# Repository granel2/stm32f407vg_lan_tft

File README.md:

# stm32f407vg_lan_tft

STM32F407VGT6 + LAN8720 (Ethernet, lwIP, DHCP, TCP-клиент) + 3.5" TFT-дисплей.
Проект основан на `stm32f407vg_lan_v1` (Ethernet-часть отлажена и работает, см. `docs/`).

## Структура

| Путь | Что это |
|---|---|
| `Core/Inc`, `Core/Src`, `Core/Startup` | Ethernet/lwIP-часть: HAL MSP, прерывания, lwIP-порт (`ethernetif.c`), TCP-клиент, `main.c` |
| `Display/` | Весь дисплейный модуль, обособлен от Ethernet-кода — см. `Display/README.md` |
| `Config/` | Постоянные настройки (сервер/имя/статический IP) + веб-страница настройки `http://<IP модуля>/` (порт 80) + TCP-конфигуратор на порту 7000 — см. `Config/README.md` |
| `Keypad/` | Приём пакетов от модуля клавиатуры 4×4 (ATmega328P) на SV5: I2C1-ведомый `0x30`, на регистрах — см. `Keypad/README.md` |
| `Drivers/` | STM32Cube HAL F4 V1.28.3, CMSIS, драйвер PHY lan8742 |
| `Middlewares/Third_Party/LwIP` | lwIP (NO_SYS=1) |
| `CMakeLists.txt`, `CMakePresets.json`, `toolchain-arm-none-eabi.cmake`, `linker_script.ld` | Сборка |
| `stm32f407vg_lan_tft.ioc`, `.mxproject` | Проект CubeMX — **только справочно**: ETH и часть периферии добавлены руками, перегенерировать код из CubeMX нельзя |
| `hardware/` | `BOARD.md` — выжимка по плате (разъёмы, питание, выводы); схема и плата (Eagle) `f407.sch`/`f407.brd`, распечатка схемы `f407_schematic_A3.pdf` |
| `docs/` | История отладки Ethernet (`PROJECT_GUIDE.md`), аппаратный фикс LAN8720 (`CHANGES_LAN8720.md`), заметки по сборке, даташиты |
| `stm32f407vg_lan_tft.code-workspace` | Workspace VS Code |

## Целевая платформа

- MCU STM32F407VGT6 (LQFP100), HSE 25 MHz, SYSCLK 160 MHz, APB1 40 MHz, APB2 80 MHz
- USART1 (PA9/PA10) и USART3 (PD8/PD9), 921600 baud — отладочный лог
- ETH RMII → LAN8720 (REFCLK на PA1), см. `docs/CHANGES_LAN8720.md` про обязательный резистор 1 кОм на страпе nINTSEL
- LED: PB4, PB5, PD0, PD1, PD4, PD7

## Сборка

Требуется `arm-none-eabi-gcc`, `cmake ≥ 3.24`, `ninja`, `openocd` в `PATH`.

```powershell
cmake --preset default          # конфигурация (build/, Ninja, toolchain-файл)
cmake --build --preset default  # сборка → build/stm32f407vg_lan_tft.{elf,bin,hex,map}
```

В VS Code: `Terminal → Run Task → CMake: Configure`, затем `CMake: Build` (Ctrl+Shift+B).

## Прошивка и отладка

- Задача VS Code `Flash STM32F407VG` — `scripts/flash-progress.ps1`, обёртка над той же
  последовательностью OpenOCD (`init` → `reset halt` → `mass_erase` → `write_image` →
  `verify_image` → `reset run`; ST-Link). Команда `program … verify` в текущей сборке
  OpenOCD глючит — подробности в `docs/PROJECT_GUIDE.md`, поэтому по-прежнему используется
  явная последовательность, а не `program`. Обёртка добавляет текстовую шкалу прогресса
  в терминал (OpenOCD сам не печатает прогресс во время записи, только итог) — она
  ориентируется на время (калибровка ~20 с под текущий размер прошивки), реальный вывод
  OpenOCD печатается полностью после завершения.
- Есть составная задача `Build + Flash` (сборка + прошивка одной командой,
  `.vscode/tasks.json`); запускать через `Ctrl+Shift+P` → `Tasks: Run Task`. `F5`
  (Run and Debug) тоже сначала пересобирает — см. `preLaunchTask` в `launch.json`.
  Личные горячие клавиши на конкретные задачи — дело вкуса, настраиваются в
  `keybindings.json` пользователя (VS Code не поддерживает keybindings, привязанные
  к конкретному проекту, поэтому в репозитории их нет).
- Отладка: конфигурация `Cortex Debug (ST-Link)` в `launch.json` (расширение `marus25.cortex-debug`).

## TFT 3.5" ST7796S (320×480), 4-wire SPI

Весь дисплейный код, схема подключения и фото платы вынесены в **[`Display/`](Display/)** —
отдельный, не зависящий от Ethernet-части модуль, чтобы его можно было дорабатывать
(шрифты, экран сетевого статуса) не трогая `main.c`. Подробности, распиновка и порядок
включения — в [`Display/README.md`](Display/README.md).

Коротко: SPI3 (PC10/PC11/PC12, 20 МГц) + CS/DC/RST/BL на PA15/PD6/PD5/PC7, всего 2 разъёма
(SV4 + SV1). При старте `TFT_App_SmokeTest()` заливает экран R/G/B (время кадра — в USART1) и рисует тест-паттерн, затем показывает
рабочий экран статуса сети (IP/DHCP/TCP/последнее сообщение от сервера).

## Что дальше

Актуальные чек-листы — в README каждого модуля: [`Display/README.md`](Display/README.md)
(дисплей, шрифт, многостраничный экран) и [`Config/README.md`](Config/README.md)
(TCP-конфигуратор, статический IP).

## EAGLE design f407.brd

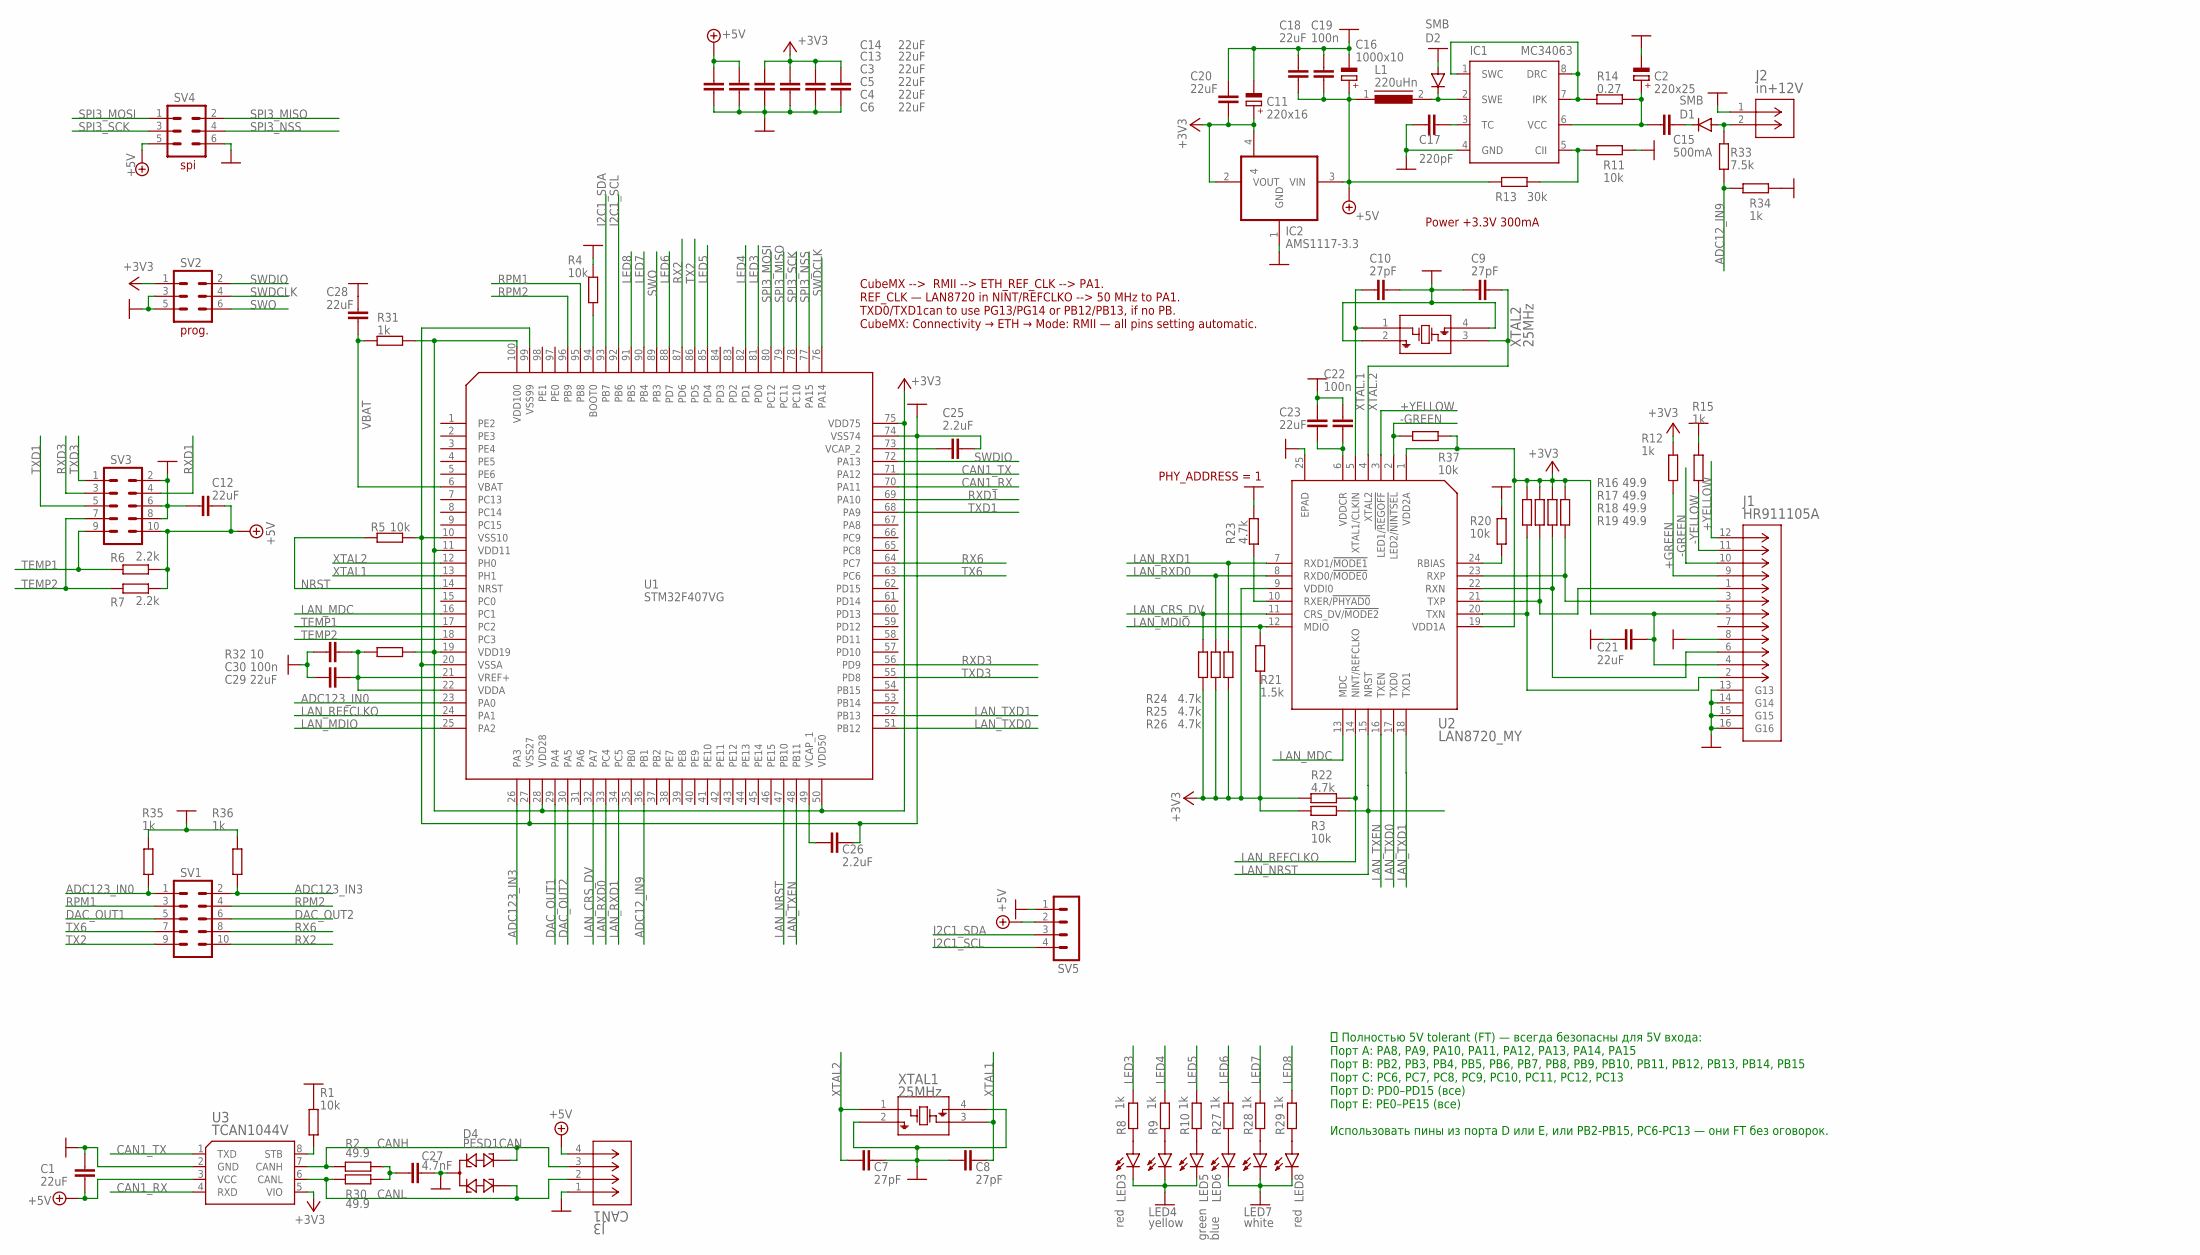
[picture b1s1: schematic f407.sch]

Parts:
C1, C3, C4, C5, C6, C12, C13, C14, C18, C20, C21, C23, C28, C29: 22uF; C0603
C2: 220x25; E3,5-8
C7, C8, C9, C10: 27pF; C0603
C11: 220x16; E2,5-7
C15: 500mA; C050-025X075
C16: 1000x10; E3,5-8
C17: 220pF; C0603
C19, C22, C30: 100n; C0603
C25, C26: 2.2uF; C0603
C27: 4.7nF; C0603
D1, D2: SMB
D4: PESD1CAN; SOT23
IC1: MC34063; 01_MY_LIB_SO08
IC2: AMS1117-3.3; GE70_DOCKING2_MYREG1117_SOT223
J1: HR911105A; CONN_1105A_HAN
J2: in+12V; CONN2_284513-2
J3: CAN1; CONN4_284513-4
L1: 220uHn; INDUCTORS_DR74
LED3, LED8: red; SML0603
LED4: yellow; SML0603
LED5: green; SML0603
LED6: blue; SML0603
LED7: white; SML0603
R1, R3, R4, R5, R11, R20, R37: 10k; R0402
R2, R16, R17, R18, R19, R30: 49.9; R0402
R6, R7: 2.2k; R0402
R8, R9, R10, R12, R15, R27, R28, R29, R31, R34, R35, R36: 1k; R0402
R13: 30k; R0402
R14: 0.27; R0805
R21: 1.5k; R0402
R22, R23, R24, R25, R26: 4.7k; R0402
R32: 10; R0402
R33: 7.5k; R0805
SV1, SV3: MA05-2
SV2, SV4: MA03-2
SV5: MA04-1
U1: STM32F407VG; MY_LQFP100
U2: LAN8720_MY; MY_QFN24
U3: TCAN1044V; MY_TCAN1044
XTAL1, XTAL2: 25MHz; ABM8_ABR

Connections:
+3V3: C3.2, C4.2, C5.2, C6.2, C11.+, C20.1, C21.1, IC2.2 (VOUT), IC2.4, J1.4, J1.5, R3.2, R12.1, R16.1, R17.1, R18.1, R19.1, R21.1, R22.2, R24.2, R25.2, R26.2, R31.2, R32.1, R37.2, SV2.1, U1.11 (VDD11), U1.19 (VDD19), U1.28 (VDD28), U1.50 (VDD50), U1.75 (VDD75), U1.100 (VDD100), U2.1 (VDD2A), U2.9 (VDDI0), U2.19 (VDD1A), U3.5 (VIO)
+5V: C1.1, C12.1, C13.2, C14.2, C16.+, C18.1, C19.1, IC2.3 (VIN), J3.4, L1.1, R6.2, R7.2, R13.1, SV3.10, SV4.5, SV5.2, U3.3 (VCC)
+GREEN: J1.9, R12.2
+YELLOW: J1.12, U2.3 (LED1/!REGOFF)
-GREEN: J1.10, R37.1, U2.2 (LED2/!NINTSEL)
-YELLOW: J1.11, R15.2
ADC12_IN9: R33.2, R34.1, U1.36 (PB1)
ADC123_IN0: R35.1, SV1.1, U1.23 (PA0)
ADC123_IN3: R36.1, SV1.2, U1.26 (PA3)
CAN1_RX: U1.70 (PA11), U3.4 (RXD)
CAN1_TX: U1.71 (PA12), U3.1 (TXD)
CANH: D4.2, J3.3, R2.1, U3.7 (CANH)
CANL: D4.1, J3.2, R30.1, U3.6 (CANL)
DAC_OUT1: SV1.5, U1.29 (PA4)
DAC_OUT2: SV1.6, U1.30 (PA5)
GND: C1.2, C2.-, C3.1, C4.1, C5.1, C6.1, C7.1, C8.2, C9.1, C10.2, C11.-, C12.2, C13.1, C14.1, C16.-, C17.2, C18.2, C19.2, C20.2, C21.2, C22.1, C23.1, C25.1, C26.1, C27.1, C28.1, C29.2, C30.2, D2.A, D4.3, IC1.4 (GND), IC2.1 (GND), J1.8, J1.13 (G13), J1.14 (G14), J1.15 (G15), J1.16 (G16), J2.1, J3.1, LED3.C, LED4.C, LED5.C, LED6.C, LED7.C, LED8.C, R1.1, R4.1, R5.2, R11.2, R15.1, R20.1, R23.2, R34.2, R35.2, R36.2, SV2.3, SV2.5, SV3.2, SV3.6, SV3.8, SV4.6, SV5.1, U1.10 (VSS10), U1.20 (VSSA), U1.27 (VSS27), U1.74 (VSS74), U1.99 (VSS99), U2.25 (EPAD), U3.2 (GND), XTAL1.2, XTAL1.4, XTAL2.2, XTAL2.4
I2C1_SCL: SV5.4, U1.92 (PB6)
I2C1_SDA: SV5.3, U1.93 (PB7)
LAN_CRS_DV: R24.1, U1.32 (PA7), U2.11 (CRS_DV/!MODE2)
LAN_MDC: U1.16 (PC1), U2.13 (MDC)
LAN_MDIO: R21.2, U1.25 (PA2), U2.12 (MDIO)
LAN_NRST: R3.1, U1.47 (PB10), U2.15 (NRST)
LAN_REFCLKO: R22.1, U1.24 (PA1), U2.14 (NINT/REFCLKO)
LAN_RXD0: R25.1, U1.33 (PC4), U2.8 (RXD0/!MODE0)
LAN_RXD1: R26.1, U1.34 (PC5), U2.7 (RXD1/!MODE1)
LAN_TXD0: U1.51 (PB12), U2.17 (TXD0)
LAN_TXD1: U1.52 (PB13), U2.18 (TXD1)
LAN_TXEN: U1.48 (PB11), U2.16 (TXEN)
LED3: R8.1, U1.81 (PD0)
LED4: R9.1, U1.82 (PD1)
LED5: R10.1, U1.85 (PD4)
LED6: R27.1, U1.88 (PD7)
LED7: R28.1, U1.90 (PB4)
LED8: R29.1, U1.91 (PB5)
unnamed: LED3.A, R8.2
unnamed: D1.A, J2.2, R33.1
unnamed: C15.2, D1.C
unnamed: LED4.A, R9.2
unnamed: C2.+, C15.1, IC1.6 (VCC), R14.2
unnamed: LED5.A, R10.2
unnamed: IC1.1 (SWC), IC1.7 (IPK), IC1.8 (DRC), R14.1
unnamed: C29.1, C30.1, R32.2, U1.21 (VREF+), U1.22 (VDDA)
unnamed: C17.1, IC1.3 (TC)
unnamed: D2.C, IC1.2 (SWE), L1.2
unnamed: IC1.5 (CII), R11.1, R13.2
unnamed: J1.3, R19.2, U2.23 (RXP)
unnamed: J1.6, R18.2, U2.22 (RXN)
unnamed: R20.2, U2.24 (RBIAS)
unnamed: J1.2, R16.2, U2.20 (TXN)
unnamed: C22.2, C23.2, U2.6 (VDDCR)
unnamed: R4.2, U1.94 (BOOT0)
unnamed: J1.1, R17.2, U2.21 (TXP)
unnamed: R23.1, U2.10 (RXER/!PHYAD0)
unnamed: C25.2, U1.73 (VCAP_2)
unnamed: C26.2, U1.49 (VCAP_1)
unnamed: C27.2, R2.2, R30.2
unnamed: LED6.A, R27.2
unnamed: LED7.A, R28.2
unnamed: LED8.A, R29.2
unnamed: R1.2, U3.8 (STB)
NRST: R5.1, U1.14 (NRST)
RPM1: SV1.3, U1.95 (PB8)
RPM2: SV1.4, U1.96 (PB9)
RX2: SV1.10, U1.87 (PD6)
RX6: SV1.8, U1.64 (PC7)
RXD1: SV3.4, U1.69 (PA10)
RXD3: SV3.3, U1.56 (PD9)
SPI3_MISO: SV4.2, U1.79 (PC11)
SPI3_MOSI: SV4.1, U1.80 (PC12)
SPI3_NSS: SV4.4, U1.77 (PA15)
SPI3_SCK: SV4.3, U1.78 (PC10)
SWDCLK: SV2.4, U1.76 (PA14)
SWDIO: SV2.2, U1.72 (PA13)
SWO: SV2.6, U1.89 (PB3)
TEMP1: R6.1, SV3.9, U1.17 (PC2)
TEMP2: R7.1, SV3.7, U1.18 (PC3)
TX2: SV1.9, U1.86 (PD5)
TX6: SV1.7, U1.63 (PC6)
TXD1: SV3.5, U1.68 (PA9)
TXD3: SV3.1, U1.55 (PD8)
VBAT: C28.2, R31.1, U1.6 (VBAT)
XTAL1: C8.1, U1.13 (PH1), XTAL1.3
XTAL2: C7.2, U1.12 (PH0), XTAL1.1
XTAL.1: C10.1, U2.5 (XTAL1/CLKIN), XTAL2.1
XTAL.2: C9.2, U2.4 (XTAL2), XTAL2.3

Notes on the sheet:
prog.
spi
Power +3.3V 300mA
PHY_ADDRESS = 1
CubeMX --> RMII --> ETH_REF_CLK --> PA1. REF_CLK — LAN8720 in NINT/REFCLKO --> 50 MHz to PA1. TXD0/TXD1can to use PG13/PG14 or PB12/PB13, if no PB. CubeMX: Connectivity → ETH → Mode: RMII — all pins setting automatic.
✅ Полностью 5V tolerant (FT) — всегда безопасны для 5V входа: Порт A: PA8, PA9, PA10, PA11, PA12, PA13, PA14, PA15 Порт B: PB2, PB3, PB4, PB5, PB6, PB7, PB8, PB9, PB10, PB11, PB12, PB13, PB14, PB15 Порт C: PC6, PC7, PC8, PC9, PC10, PC11, PC12, PC13 Порт D: PD0–PD15 (все) Порт E: PE0–PE15 (все) Испо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

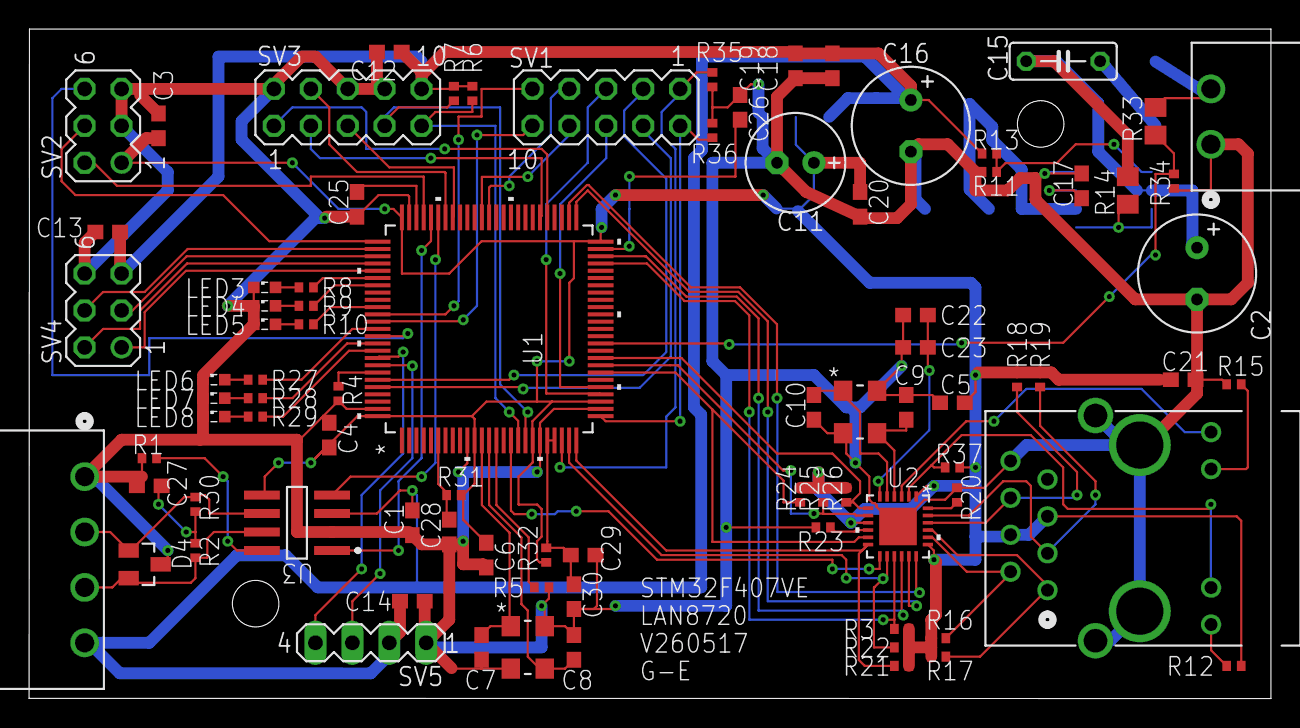
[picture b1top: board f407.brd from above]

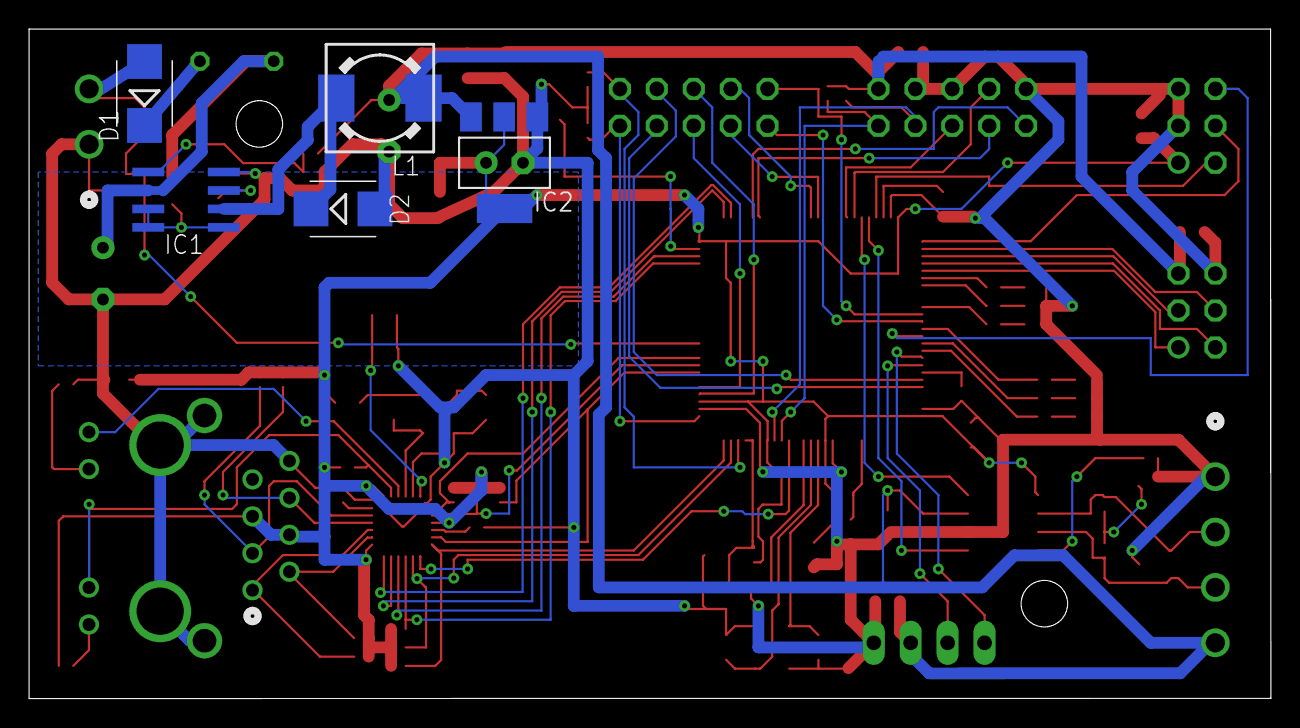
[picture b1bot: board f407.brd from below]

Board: 2 copper layers, 85.4 x 46.1 mm, 91 parts (5 on the bottom side), 85 nets.

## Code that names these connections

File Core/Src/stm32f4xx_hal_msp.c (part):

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
    __HAL_RCC_GPIOA_CLK_ENABLE();
    /**USART1 GPIO Configuration
    PA9     ------> USART1_TX
    PA10     ------> USART1_RX
    */
    GPIO_InitStruct.Pin = GPIO_PIN_9|GPIO_PIN_10;
    GPIO_InitStruct.Mode = GPIO_MODE_AF_PP;
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
    __HAL_RCC_GPIOD_CLK_ENABLE();
    /**USART3 GPIO Configuration
    PD8     ------> USART3_TX
    PD9     ------> USART3_RX
    */
    GPIO_InitStruct.Pin = GPIO_PIN_8|GPIO_PIN_9;
    GPIO_InitStruct.Mode = GPIO_MODE_AF_PP;
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    __HAL_RCC_USART1_CLK_DISABLE();

    /**USART1 GPIO Configuration
    PA9     ------> USART1_TX
    PA10     ------> USART1_RX
    */
    HAL_GPIO_DeInit(GPIOA, GPIO_PIN_9|GPIO_PIN_10);

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    __HAL_RCC_USART3_CLK_DISABLE();

    /**USART3 GPIO Configuration
    PD8     ------> USART3_TX
    PD9     ------> USART3_RX
    */
    HAL_GPIO_DeInit(GPIOD, GPIO_PIN_8|GPIO_PIN_9);

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  * @brief ETH MSP Initialization
  * This function configures the RMII pins for the on-board LAN8720 (see
  * f407.sch - matches CubeMX's default ETH/RMII pin assignment exactly) and
  * issues a clean reset pulse to the PHY via its NRST line (PB10).
  *
  * NOTE: ETH is not declared in stm32f407vg_lan_tft.ioc (it was wired up by
  * hand, see PROJECT_GUIDE.md), so this lives inside the USER CODE block on
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    __HAL_RCC_GPIOC_CLK_ENABLE();

    /**ETH GPIO Configuration
    PA1     ------> ETH_RMII_REF_CLK
    PA2     ------> ETH_RMII_MDIO
    PA7     ------> ETH_RMII_CRS_DV
    PB11     ------> ETH_RMII_TX_EN
    PB12     ------> ETH_RMII_TXD0
    PB13     ------> ETH_RMII_TXD1
    PC1     ------> ETH_RMII_MDC
    PC4     ------> ETH_RMII_RXD0
    PC5     ------> ETH_RMII_RXD1
    */
    GPIO_InitStruct.Mode = GPIO_MODE_AF_PP;
    GPIO_InitStruct.Pull = GPIO_NOPULL;
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    GPIO_InitStruct.Pin = GPIO_PIN_1 | GPIO_PIN_4 | GPIO_PIN_5;
    HAL_GPIO_Init(GPIOC, &GPIO_InitStruct);

    /* LAN8720 NRST (PB10). On this board it's pulled up to 3V3 through R3
       (10k) so the PHY normally comes out of reset on its own as power
       ramps up, but PB10 is wired in parallel with that resistor so
       firmware can force a clean reset pulse on every boot instead of
       depending on the supply ramp timing. */
    GPIO_InitStruct.Pin = GPIO_PIN_10;
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    HAL_Delay(2000);
    HAL_GPIO_WritePin(GPIOB, GPIO_PIN_10, GPIO_PIN_SET);
    /* LAN8720 crystal oscillator needs ~10-20ms to stabilize after nRST.
       Without a stable 50 MHz CLK_OUT on PA1 the ETH DMA SW reset
       (DMABMR.SWR) never completes. 100 ms is safe across all variants. */
    HAL_Delay(100);

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    __HAL_RCC_ETH_CLK_ENABLE();

    /* MDIO probe + PHY soft-reset.
       The RMII 50 MHz REF_CLK on PA1 must be active before DMABMR.SWR can
       clear.  We scan MDIO, read key registers, and issue a BCR soft-reset to
       restart the LAN8720's crystal oscillator / PLL → enables CLKOUT.
       CR[4:2]=0x14 = Div102 for 160 MHz HCLK (MDC ≈ 1.57 MHz). */
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
/**
  * @brief SPI3 MSP Initialization - TFT bus on the SV4 header
  * PC10 -> SPI3_SCK, PC11 -> SPI3_MISO, PC12 -> SPI3_MOSI (AF6).
  * NSS is software-driven (PA15 as plain GPIO, set up in MX_GPIO_Init).
  * TX DMA: DMA1 Stream5 / Channel 0, half-words, memory increment OFF -
  * ST7796S_FillRect() streams one colour word, SPI in 16-bit frames.
  * SPI3_IRQn is deliberately NOT enabled: in 2-line mode the unread RX side
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
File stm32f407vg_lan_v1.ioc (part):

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Mcu.Name=STM32F407V(E-G)Tx
Mcu.Package=LQFP100
Mcu.UserName=STM32F407VGTx
PA10.Mode=Asynchronous
PA10.Signal=USART1_RX
PA13.Mode=Serial_Wire
PA13.Signal=SYS_JTMS-SWDIO
PA14.Mode=Serial_Wire
PA14.Signal=SYS_JTCK-SWCLK
PA9.Mode=Asynchronous
PA9.Signal=USART1_TX
PB4.GPIOParameters=GPIO_Label
PB4.GPIO_Label=LED7
PB4.Signal=GPIO_Output
PB5.GPIOParameters=GPIO_Label
PB5.GPIO_Label=LED8
PB5.Signal=GPIO_Output
PD0.GPIOParameters=GPIO_Label
PD0.GPIO_Label=LED3
PD0.Signal=GPIO_Output
PD1.GPIOParameters=GPIO_Label
PD1.GPIO_Label=LED4
PD1.Signal=GPIO_Output
PD4.GPIOParameters=GPIO_Label
PD4.GPIO_Label=LED5
PD4.Signal=GPIO_Output
PD7.GPIOParameters=GPIO_Label
PD7.GPIO_Label=LED6
PD7.Signal=GPIO_Output
PD8.Mode=Asynchronous
PD8.Signal=USART3_TX
PD9.Mode=Asynchronous
PD9.Signal=USART3_RX
PH0-OSC_IN.Mode=HSE-External-Oscillator
PH0-OSC_IN.Signal=RCC_OSC_IN
PH1-OSC_OUT.Mode=HSE-External-Oscillator
PH1-OSC_OUT.Signal=RCC_OSC_OUT
RCC.HSE_VALUE=25000000
RCC.SYSCLKFreq_VALUE=160000000
RCC.SYSCLKSource=RCC_SYSCLKSOURCE_PLLCLK
board=custom

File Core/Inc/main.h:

/* USER CODE BEGIN Header */
/**
  ******************************************************************************
  * @file           : main.h
  * @brief          : Header for main.c file.
  *                   This file contains the common defines of the application.
  ******************************************************************************
  * @attention
  *
  * Copyright (c) 2026 STMicroelectronics.
  * All rights reserved.
  *
  * This software is licensed under terms that can be found in the LICENSE file
  * in the root directory of this software component.
  * If no LICENSE file comes with this software, it is provided AS-IS.
  *
  ******************************************************************************
  */
/* USER CODE END Header */

/* Define to prevent recursive inclusion -------------------------------------*/
#ifndef __MAIN_H
#define __MAIN_H

#ifdef __cplusplus
extern "C" {
#endif

/* Includes ------------------------------------------------------------------*/
#include "stm32f4xx_hal.h"

/* Private includes ----------------------------------------------------------*/
/* USER CODE BEGIN Includes */

/* USER CODE END Includes */

/* Exported types ------------------------------------------------------------*/
/* USER CODE BEGIN ET */

/* USER CODE END ET */

/* Exported constants --------------------------------------------------------*/
/* USER CODE BEGIN EC */

/* USER CODE END EC */

/* Exported macro ------------------------------------------------------------*/
/* USER CODE BEGIN EM */

/* USER CODE END EM */

/* Exported functions prototypes ---------------------------------------------*/
void Error_Handler(void);

/* USER CODE BEGIN EFP */
/* Shared debug logger (USART1, 921600 baud) - defined in main.c, used from
   here and from Display/Src/tft_app.c. */
void Debug_Print(const char *msg);
/* USER CODE END EFP */

/* Private defines -----------------------------------------------------------*/
#define LED3_Pin GPIO_PIN_0
#define LED3_GPIO_Port GPIOD
#define LED4_Pin GPIO_PIN_1
#define LED4_GPIO_Port GPIOD
#define LED5_Pin GPIO_PIN_4
#define LED5_GPIO_Port GPIOD
#define LED6_Pin GPIO_PIN_7
#define LED6_GPIO_Port GPIOD
#define LED7_Pin GPIO_PIN_4
#define LED7_GPIO_Port GPIOB
#define LED8_Pin GPIO_PIN_5
#define LED8_GPIO_Port GPIOB

/* USER CODE BEGIN Private defines */
/* 3.5" ST7796S TFT on SPI3 (PC10 SCK / PC11 MISO / PC12 MOSI, header SV4).
   CS is a plain GPIO on SV4; DC/RST/BL are plain GPIOs grouped on three
   adjacent SV1 pins (8/9/10) - see Display/README.md and
   Display/docs/TFT_WIRING.md. PC7/PD5/PD6 are silkscreened USART6/USART2
   TX-RX on this board (hardware/BOARD.md) but neither UART is used by
   this firmware, so they're free to repurpose as plain outputs - same
   precedent as PB8/BL. PC7 needs its GPIOC clock enabled explicitly
   (TFT_App_GPIO_Init() does this) since MX_GPIO_Init() doesn't otherwise
   turn it on before this runs. */
#define TFT_CS_Pin GPIO_PIN_15
#define TFT_CS_GPIO_Port GPIOA
#define TFT_DC_Pin GPIO_PIN_6
#define TFT_DC_GPIO_Port GPIOD
#define TFT_RST_Pin GPIO_PIN_5
#define TFT_RST_GPIO_Port GPIOD
#define TFT_BL_Pin GPIO_PIN_7
#define TFT_BL_GPIO_Port GPIOC
/* Page-switch button, SV1.7 (PC6, silkscreened USART6_TX - unused). Wired
   to GND on press; TFT_App_GPIO_Init() configures the internal pull-up
   (GPIO_PULLUP), so no external pull-up resistor is needed - just a
   switch/button between this pin and GND. */
#define TFT_PAGEBTN_Pin GPIO_PIN_6
#define TFT_PAGEBTN_GPIO_Port GPIOC
/* USER CODE END Private defines */

#ifdef __cplusplus
}
#endif

#endif /* __MAIN_H */

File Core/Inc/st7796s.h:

/**
  ******************************************************************************
  * @file    st7796s.h
  * @brief   Minimal ST7796S driver (3.5" 320x480 TFT) over 4-wire SPI.
  *
  * Wiring (module "SPI" header <-> board headers, see hardware/f407.sch):
  *   SCL   -> PC10 SPI3_SCK   (SV4.3)
  *   SDA   -> PC12 SPI3_MOSI  (SV4.1)
  *   SDA-O -> PC11 SPI3_MISO  (SV4.2)   optional, only needed for ReadID
  *   CS    -> PA15            (SV4.4)   software-driven GPIO
  *   DC    -> PB6             (SV5.4)
  *   RST   -> PB7             (SV5.3)
  *   BL    -> PB8             (SV1.3)   high = backlight on
  *   GND   -> GND             (SV4.6)
  *   VCC   -> +5V             (SV4.5)   module must have its own 3.3 V LDO;
  *                                        otherwise +3V3 from SV2.1
  * Module IM0..IM2 solder jumpers must be set to the "SPI" (4-wire) column.
  ******************************************************************************
  */

#ifndef ST7796S_H
#define ST7796S_H

#ifdef __cplusplus
extern "C" {
#endif

#include "main.h"

/* Panel geometry in the default (portrait, MADCTL rotation 0) orientation */
#define ST7796S_WIDTH   320U
#define ST7796S_HEIGHT  480U

/* RGB565 helpers */
#define ST7796S_RGB(r, g, b) \
  ((uint16_t)((((uint16_t)(r) & 0xF8U) << 8) | (((uint16_t)(g) & 0xFCU) << 3) | ((uint16_t)(b) >> 3)))
#define ST7796S_BLACK   0x0000U
#define ST7796S_WHITE   0xFFFFU
#define ST7796S_RED     0xF800U
#define ST7796S_GREEN   0x07E0U
#define ST7796S_BLUE    0x001FU
#define ST7796S_YELLOW  0xFFE0U
#define ST7796S_CYAN    0x07FFU
#define ST7796S_MAGENTA 0xF81FU

void     ST7796S_Init(SPI_HandleTypeDef *hspi);
void     ST7796S_Backlight(uint8_t on);
/* Rotation 0..3 = portrait, landscape, portrait flipped, landscape flipped */
void     ST7796S_SetRotation(uint8_t rotation);
uint16_t ST7796S_Width(void);
uint16_t ST7796S_Height(void);

/* Reads RDID4 (0xD3): 4 raw bytes, ST7796S answers xx 00 77 96. Needs SDA-O
   wired to PC11. Returns the raw bytes so a log can show exactly what came
   back (a 1-bit shift is normal for this controller in 4-wire SPI). */
void     ST7796S_ReadID(uint8_t out[4]);

void     ST7796S_FillScreen(uint16_t color);
void     ST7796S_FillRect(uint16_t x, uint16_t y, uint16_t w, uint16_t h, uint16_t color);
/* Hardware smoke test: colour bars, white border and a checkerboard corner.
   Wrong colours / mirrored layout tell which MADCTL bits the panel needs. */
void     ST7796S_DrawTestPattern(void);

/* 7-segment style digits drawn from rectangles - lets the bring-up show
   numbers (uptime, timings) before any real font exists. Cell is w x h px. */
void     ST7796S_DrawDigit7(uint16_t x, uint16_t y, uint16_t w, uint16_t h,
                            uint8_t digit, uint16_t color, uint16_t bg);
/* Right-aligned unsigned number, `digits` cells wide, leading zeros blanked */
void     ST7796S_DrawNumber7(uint16_t x, uint16_t y, uint16_t w, uint16_t h,
                             uint32_t value, uint8_t digits, uint16_t color, uint16_t bg);

#ifdef __cplusplus
}
#endif

#endif /* ST7796S_H */

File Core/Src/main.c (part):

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  HAL_Init();

  /* USER CODE BEGIN Init */
  /* Hold the LAN8720 in reset (PB10/nRST) as early as firmware can run, before
     R3's 10k pull-up can release it on its own while VDD/clocks are still
     ramping up. Previously nRST wasn't touched by firmware until deep inside
     HAL_ETH_MspInit() (called from MX_LWIP_Init() below), well after
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    Error_Handler();
  }

  /* MCO1 (PA8) = HSE/1 = 25 MHz: backup reference for LAN8720 XTAL1/CLKIN.
     The onboard 25 MHz crystal (XTAL2, near LAN8720) drives U2 pad 5 via the
     XTAL.1 net.  If that crystal is absent or defective, LAN8720 has no PLL
     reference and NINT/REFCLKO stays silent → DMABMR.SWR never clears.
     HAL_RCC_MCOConfig configures PA8 GPIO automatically (AF0 push-pull VH).
     HARDWARE (only needed if crystal is bad/absent):
       connect a short wire from PA8 (STM32 pin 67) to XTAL2 crystal pad 1
       (the pad on the XTAL.1 net = LAN8720 XTAL1/CLKIN side, NOT the XTAL2 side). */
  HAL_RCC_MCOConfig(RCC_MCO1, RCC_MCO1SOURCE_HSE, RCC_MCODIV_1);
}
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  __HAL_RCC_GPIOB_CLK_ENABLE();

  /*Configure GPIO pin Output Level */
  HAL_GPIO_WritePin(GPIOD, LED3_Pin|LED4_Pin|LED5_Pin|LED6_Pin, GPIO_PIN_RESET);

  /*Configure GPIO pin Output Level */
  HAL_GPIO_WritePin(GPIOB, LED7_Pin|LED8_Pin, GPIO_PIN_RESET);

  /*Configure GPIO pins : LED3_Pin LED4_Pin LED5_Pin LED6_Pin */
  GPIO_InitStruct.Pin = LED3_Pin|LED4_Pin|LED5_Pin|LED6_Pin;
  GPIO_InitStruct.Mode = GPIO_MODE_OUTPUT_PP;
  GPIO_InitStruct.Pull = GPIO_NOPULL;
  GPIO_InitStruct.Speed = GPIO_SPEED_FREQ_LOW;
  HAL_GPIO_Init(GPIOD, &GPIO_InitStruct);

  /*Configure GPIO pins : LED7_Pin LED8_Pin */
  GPIO_InitStruct.Pin = LED7_Pin|LED8_Pin;
  GPIO_InitStruct.Mode = GPIO_MODE_OUTPUT_PP;
  GPIO_InitStruct.Pull = GPIO_NOPULL;
  GPIO_InitStruct.Speed = GPIO_SPEED_FREQ_LOW;
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    uint16_t pin;
  } leds[6] =
  {
    {GPIOD, LED3_Pin}, {GPIOD, LED4_Pin}, {GPIOD, LED5_Pin},
    {GPIOD, LED6_Pin}, {GPIOB, LED7_Pin}, {GPIOB, LED8_Pin},
  };
  static uint8_t current = 0;
  static uint32_t next_tick = 0;
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
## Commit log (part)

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2026-06-18 2026.06.18 good test
2026-06-18 2026.06.18 fix dhcp long time ago
2026-06-19 Shorten nRST/retry/DHCP timeouts now that strap mis-latch is the confirmed root cause
    The long nRST hold (5s), 3x init retry, and 5s MDIO power-down hold were
    defensive measures for a disproven "unfixable PHY lockup" theory. With the
    real cause fixed in hardware (nINTSEL strap pulldown 6.8k->1k, confirmed
    against Microchip's own EVB8720 reference schematic), trim them back so
    recovery cycles take seconds instead of minutes. Also shortens the
    DHCP-stuck watchdog and reset-escalation threshold, since soft
2026-06-19 2026.06.19 server ok

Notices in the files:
parts and their libraries:
COPYRIGHT: Copyright (C) 2026 Ultra Librarian. All rights reserved.
